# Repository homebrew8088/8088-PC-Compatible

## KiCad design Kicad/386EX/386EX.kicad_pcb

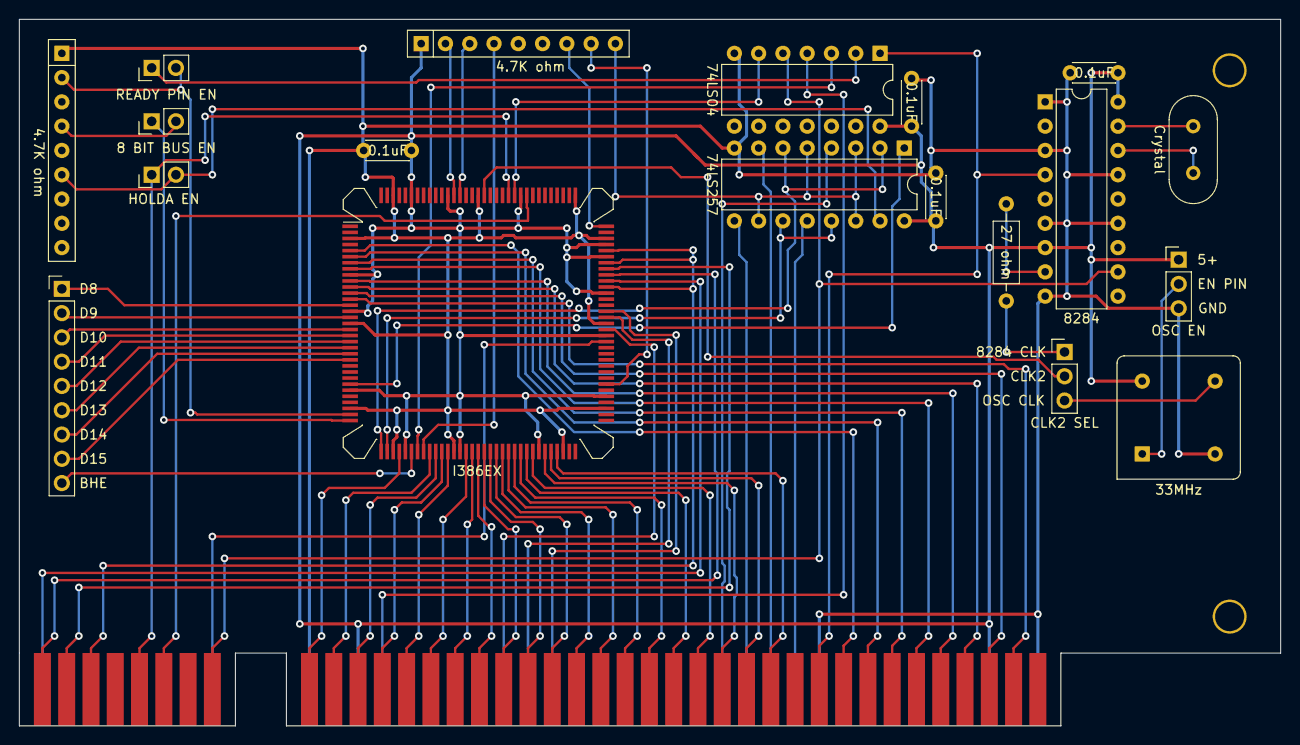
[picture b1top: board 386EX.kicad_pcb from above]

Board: 2 copper layers, 132.0 x 73.9 mm, 23 parts (0 on the bottom side), 79 nets.

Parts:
8_BIT_BUS_EN1: 8 BIT BUS EN; PinHeader_1x02_P2.54mm_Vertical
C1, C2, C3, C4: 0.1uF; C_Disc_D4.3mm_W1.9mm_P5.00mm
CLK2_SEL1: CLK2 SEL; PinHeader_1x03_P2.54mm_Vertical
HOLDA_EN1: HOLDA EN; PinHeader_1x02_P2.54mm_Vertical
J1: Conn_02x08_Counter_Clockwise; 16_EDGE_CARD_BUS
J2: Bus_ISA_8bit; BUS_8_BIT
J8: Conn_01x09; PinHeader_1x09_P2.54mm_Vertical
OSC_EN1: OSC EN; PinHeader_1x03_P2.54mm_Vertical
R: L; Large_Via
R1, R7: 4.7K ohm; R_Array_SIP9
R3: 27 ohm; R_Axial_DIN0207_L6.3mm_D2.5mm_P10.16mm_Horizontal
R#2: L; Large_Via
READY_PIN_EN1: READY PIN EN; PinHeader_1x02_P2.54mm_Vertical
U1: I386EX; PQFP-132_24x24mm_P0.635mm_i386
U2: 8284; DIP-18_W7.62mm
U3: 74LS257; DIP-16_W7.62mm
U4: 74LS04; DIP-14_W7.62mm
X1: 33MHz; Oscillator_DIP-8
Y1: Crystal; Crystal_HC18-U_Vertical

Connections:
/5+: C1.2, C2.2, C3.2, C4.2, J2.3, J2.29, OSC_EN1.1, R7.1, U1.9, U1.15, U1.28, U1.38, U1.47, U1.60, U1.71, U1.81, U1.88, U1.94, U1.96, U1.109, U1.121, U1.127, U2.7, U2.18, U3.16, U4.14, X1.8
/8_BIT_EN: 8_BIT_BUS_EN1.2, R1.4
/8_BIT_EN_JMP: 8_BIT_BUS_EN1.1, U1.33
/8284_OUT: CLK2_SEL1.1, R3.2
/A0: J2.62, U1.37
/A1: J2.61, U1.42
/A2: J2.60, U1.43
/A3: J2.59, U1.44
/A4: J2.58, U1.45
/A5: J2.57, U1.48
/A6: J2.56, U1.49
/A7: J2.55, U1.50
/A8: J2.54, U1.51
/A9: J2.53, U1.52
/A10: J2.52, U1.53
/A11: J2.51, U1.54
/A12: J2.50, U1.55
/A13: J2.49, U1.56
/A14: J2.48, U1.57
/A15: J2.47, U1.58
/A16: J2.46, U1.59
/A17: J2.45, U1.61
/A18: J2.44, U1.62
/A19: J2.43, U1.63
/ALE: J2.28, U4.4
/ALE_: U1.40, U4.3
/BHE: J8.9, U1.39
/CLK1: R3.1, U2.8
/CLK2: CLK2_SEL1.2, U1.115
/D0: J2.40, U1.5
/D1: J2.39, U1.6
/D2: J2.38, U1.7
/D3: J2.37, U1.8
/D4: J2.36, U1.10
/D5: J2.35, U1.11
/D6: J2.34, U1.12
/D7: J2.33, U1.13
/D8: J8.1, U1.14
/D9: J8.2, U1.16
/D10: J8.3, U1.18
/D11: J8.4, U1.19
/D12: J8.5, U1.20
/D13: J8.6, U1.21
/D14: J8.7, U1.22
/D15: J8.8, U1.23
/FLT: R7.7, U1.99
/GND: C1.1, C2.1, C3.1, C4.1, J2.1, J2.10, J2.31, OSC_EN1.3, R1.1, U1.3, U1.17, U1.31, U1.36, U1.46, U1.64, U1.69, U1.83, U1.97, U1.100, U1.116, U1.130, U2.1, U2.3, U2.6, U2.9, U2.13, U2.15, U3.8, U4.7, X1.4
/HF_PCLK: J1.11, U1.89, U1.93, U1.95
/HOLD: J1.14, U1.108
/HOLDA: HOLDA_EN1.1, J1.13, U1.111
/HOLDA_JMP: HOLDA_EN1.2, R1.6, U3.15
/IORD: J2.14, U3.4
/IOWR: J2.13, U3.9
/IO_M: U1.27, U3.1
/IRQ1: J1.1, U1.80
/IRQ5: J2.23, U1.82
/IRQ6: J2.22, U1.84
/IRQ7: J2.21, U1.85
/MRD: J2.12, U3.7
/MWR: J2.11, U3.12
/NMI: J1.8, U1.90
/OSC_EN: OSC_EN1.2, X1.1
/OSC_OUTPUT: CLK2_SEL1.3, X1.5
/PIPELINE_EN: R7.4, U1.41
/PU_257: R7.9, U3.3, U3.5, U3.10, U3.14
/RD: U1.34, U3.2, U3.6
/RDY1: J2.41, U2.4, U4.1
/READY_: READY_PIN_EN1.1, U4.2
/READY_JMP: R1.2, READY_PIN_EN1.2, U1.32
/RESET: J1.16, U2.11, U4.5
/RESET_: U1.110, U4.6
/SMI: R7.8, U1.73
/SMIACT: R7.2, U1.120
/SPK_GO: J1.10, U1.92
/SPK_OUT: J1.9, U1.91
/TRST: R7.3, U1.119
/WR: U1.35, U3.11, U3.13
/X1: U2.17, Y1.1
/X2: U2.16, Y1.2

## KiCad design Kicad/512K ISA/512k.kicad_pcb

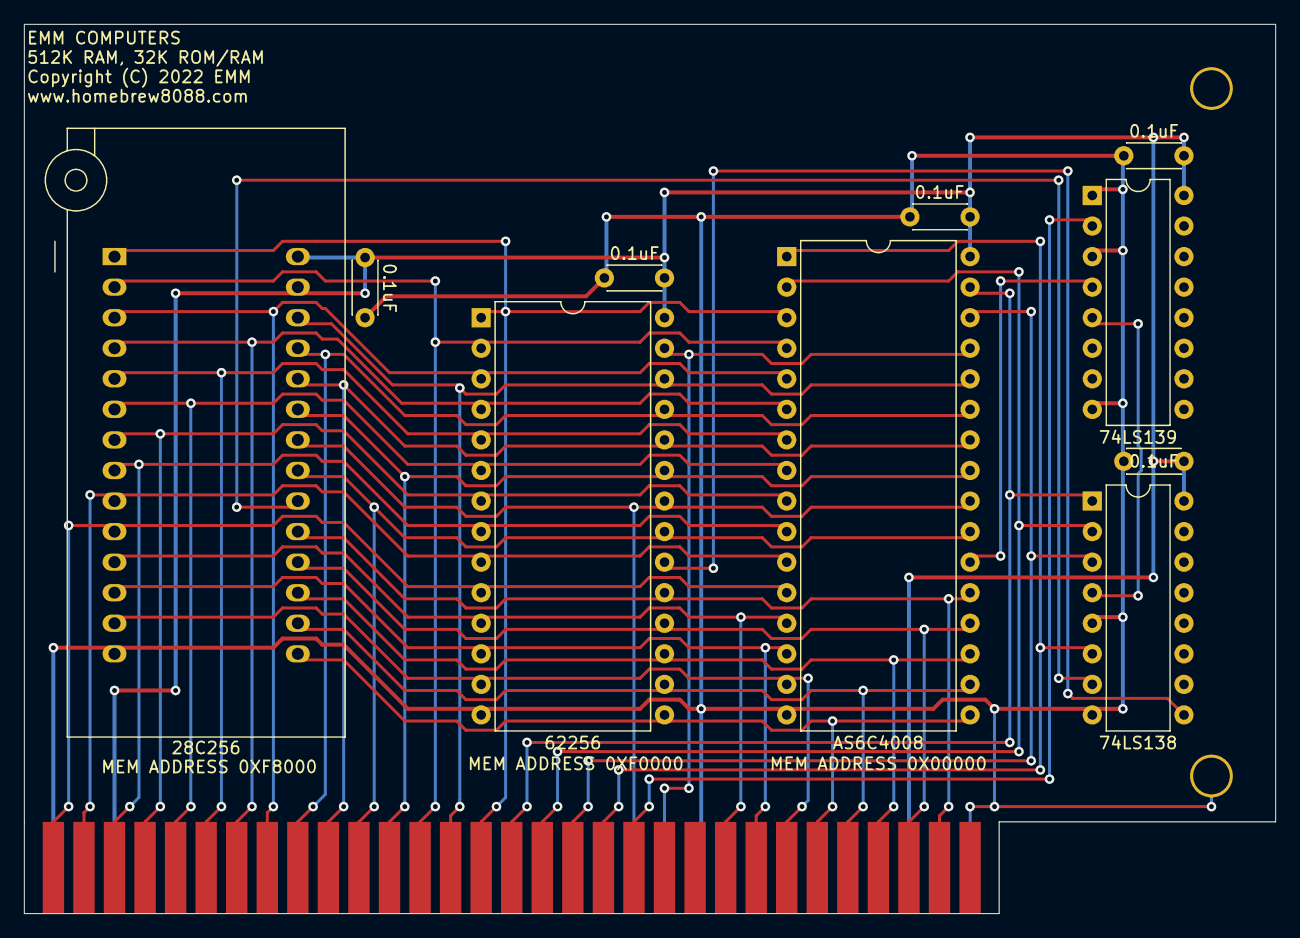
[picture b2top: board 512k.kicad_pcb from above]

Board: 2 copper layers, 104.0 x 73.9 mm, 13 parts (0 on the bottom side), 36 nets.

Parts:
C1, C2, C3, C4, C5: 0.1uF; C_Disc_D4.3mm_W1.9mm_P5.00mm
J9: Bus_ISA_8bit; BUS_8_BIT
R: L; Large_Via
R#2: L; Large_Via
U1: 62256; DIP-28_W15.24mm
U2: 28C256; DIP_Socket-28_W11.9_W12.7_W15.24_W17.78_W18.5_3M_228-1277-0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
U3: AS6C4008; DIP-32_W15.24mm
U4: 74LS139; DIP-16_W7.62mm
U5: 74LS138; DIP-16_W7.62mm

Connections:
/5+: C1.2, C2.2, C3.2, C4.2, C5.2, J9.3, J9.29, U1.28, U2.27, U2.28, U3.32, U4.16, U5.16
/32K_RAM_CS: U1.20, U5.9
/32K_ROM_CS: U2.20, U5.7
/512K_CS: U3.22, U4.4
/A0: J9.62, U1.10, U2.10, U3.12
/A1: J9.61, U1.9, U2.9, U3.11
/A2: J9.60, U1.8, U2.8, U3.10
/A3: J9.59, U1.7, U2.7, U3.9
/A4: J9.58, U1.6, U2.6, U3.8
/A5: J9.57, U1.5, U2.5, U3.7
/A6: J9.56, U1.4, U2.4, U3.6
/A7: J9.55, U1.3, U2.3, U3.5
/A8: J9.54, U1.25, U2.25, U3.27
/A9: J9.53, U1.24, U2.24, U3.26
/A10: J9.52, U1.21, U2.21, U3.23
/A11: J9.51, U1.23, U2.23, U3.25
/A12: J9.50, U1.2, U2.2, U3.4
/A13: J9.49, U1.26, U2.26, U3.28
/A14: J9.48, U1.1, U2.1, U3.3
/A15: J9.47, U3.31, U5.1
/A16: J9.46, U3.2, U5.2
/A17: J9.45, U3.30, U5.3
/A18: J9.44, U3.1, U5.6
/A19: J9.43, U4.2
/D0: J9.40, U1.11, U2.11, U3.13
/D1: J9.39, U1.12, U2.12, U3.14
/D2: J9.38, U1.13, U2.13, U3.15
/D3: J9.37, U1.15, U2.15, U3.17
/D4: J9.36, U1.16, U2.16, U3.18
/D5: J9.35, U1.17, U2.17, U3.19
/D6: J9.34, U1.18, U2.18, U3.20
/D7: J9.33, U1.19, U2.19, U3.21
/GND: C1.1, C2.1, C3.1, C4.1, C5.1, J9.1, J9.10, J9.31, R.1, U1.14, U2.14, U3.16, U4.1, U4.3, U4.8, U5.5, U5.8
/MRD: J9.12, U1.22, U2.22, U3.24
/MWR: J9.11, U1.27, U3.29
/UPPER_512K: U4.5, U5.4

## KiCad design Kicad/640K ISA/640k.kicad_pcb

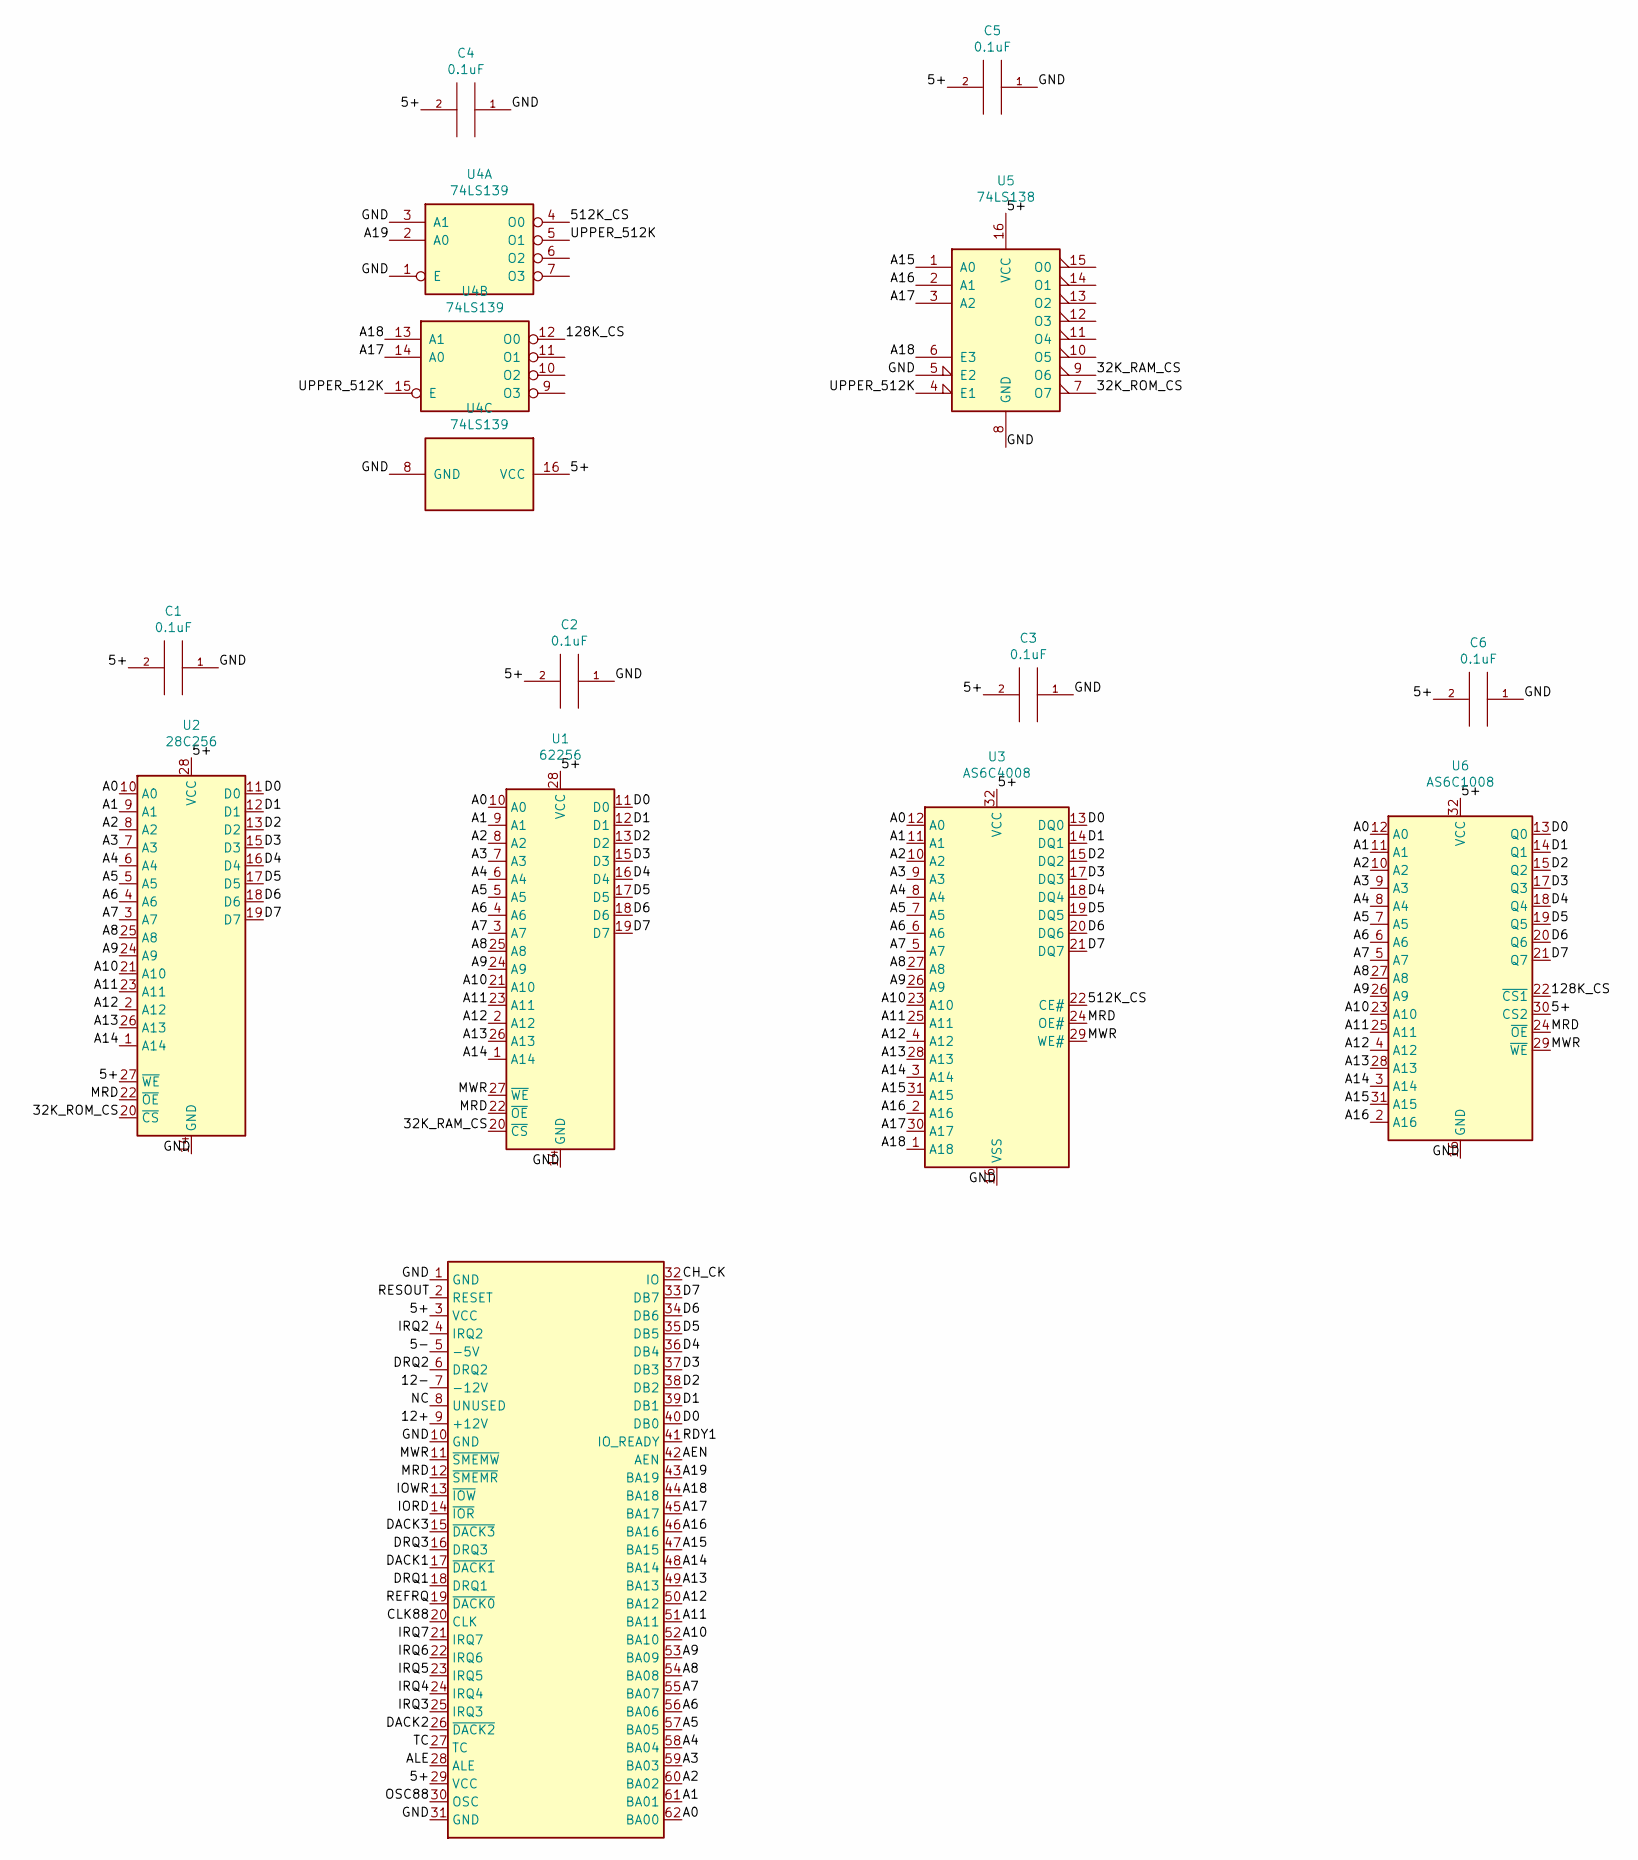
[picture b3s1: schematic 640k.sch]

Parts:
C1, C2, C3, C4, C5, C6: 0.1uF; C_Disc_D4.3mm_W1.9mm_P5.00mm
J9: Bus_ISA_8bit; BUS_8_BIT
U1: 62256; DIP-28_W15.24mm
U2: 28C256; DIP-28_W15.24mm
U3: AS6C4008; DIP-32_W15.24mm
U4: 74LS139; DIP-16_W7.62mm
U5: 74LS138; DIP-16_W7.62mm
U6: AS6C1008; DIP-32_W15.24mm

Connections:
/5+: C1.2, C2.2, C3.2, C4.2, C5.2, C6.2, J9.3 (VCC), J9.29 (VCC), U1.28 (VCC), U2.27 (~WE), U2.28 (VCC), U3.32 (VCC), U4.16 (VCC), U5.16 (VCC), U6.30 (CS2), U6.32 (VCC)
/5-: J9.5 (-5V)
/12+: J9.9 (+12V)
/12-: J9.7 (-12V)
/32K_RAM_CS: U1.20 (~CS), U5.9 (O6)
/32K_ROM_CS: U2.20 (~CS), U5.7 (O7)
/128K_CS: U4.12 (O0), U6.22 (~CS1)
/512K_CS: U3.22 (CE#), U4.4 (O0)
/A0: J9.62 (BA00), U1.10 (A0), U2.10 (A0), U3.12 (A0), U6.12 (A0)
/A1: J9.61 (BA01), U1.9 (A1), U2.9 (A1), U3.11 (A1), U6.11 (A1)
/A2: J9.60 (BA02), U1.8 (A2), U2.8 (A2), U3.10 (A2), U6.10 (A2)
/A3: J9.59 (BA03), U1.7 (A3), U2.7 (A3), U3.9 (A3), U6.9 (A3)
/A4: J9.58 (BA04), U1.6 (A4), U2.6 (A4), U3.8 (A4), U6.8 (A4)
/A5: J9.57 (BA05), U1.5 (A5), U2.5 (A5), U3.7 (A5), U6.7 (A5)
/A6: J9.56 (BA06), U1.4 (A6), U2.4 (A6), U3.6 (A6), U6.6 (A6)
/A7: J9.55 (BA07), U1.3 (A7), U2.3 (A7), U3.5 (A7), U6.5 (A7)
/A8: J9.54 (BA08), U1.25 (A8), U2.25 (A8), U3.27 (A8), U6.27 (A8)
/A9: J9.53 (BA09), U1.24 (A9), U2.24 (A9), U3.26 (A9), U6.26 (A9)
/A10: J9.52 (BA10), U1.21 (A10), U2.21 (A10), U3.23 (A10), U6.23 (A10)
/A11: J9.51 (BA11), U1.23 (A11), U2.23 (A11), U3.25 (A11), U6.25 (A11)
/A12: J9.50 (BA12), U1.2 (A12), U2.2 (A12), U3.4 (A12), U6.4 (A12)
/A13: J9.49 (BA13), U1.26 (A13), U2.26 (A13), U3.28 (A13), U6.28 (A13)
/A14: J9.48 (BA14), U1.1 (A14), U2.1 (A14), U3.3 (A14), U6.3 (A14)
/A15: J9.47 (BA15), U3.31 (A15), U5.1 (A0), U6.31 (A15)
/A16: J9.46 (BA16), U3.2 (A16), U5.2 (A1), U6.2 (A16)
/A17: J9.45 (BA17), U3.30 (A17), U4.14 (A0), U5.3 (A2)
/A18: J9.44 (BA18), U3.1 (A18), U4.13 (A1), U5.6 (E3)
/A19: J9.43 (BA19), U4.2 (A0)
/AEN: J9.42 (AEN)
/ALE: J9.28 (ALE)
/CH_CK: J9.32 (IO)
/CLK88: J9.20 (CLK)
/D0: J9.40 (DB0), U1.11 (D0), U2.11 (D0), U3.13 (DQ0), U6.13 (Q0)
/D1: J9.39 (DB1), U1.12 (D1), U2.12 (D1), U3.14 (DQ1), U6.14 (Q1)
/D2: J9.38 (DB2), U1.13 (D2), U2.13 (D2), U3.15 (DQ2), U6.15 (Q2)
/D3: J9.37 (DB3), U1.15 (D3), U2.15 (D3), U3.17 (DQ3), U6.17 (Q3)
/D4: J9.36 (DB4), U1.16 (D4), U2.16 (D4), U3.18 (DQ4), U6.18 (Q4)
/D5: J9.35 (DB5), U1.17 (D5), U2.17 (D5), U3.19 (DQ5), U6.19 (Q5)
/D6: J9.34 (DB6), U1.18 (D6), U2.18 (D6), U3.20 (DQ6), U6.20 (Q6)
/D7: J9.33 (DB7), U1.19 (D7), U2.19 (D7), U3.21 (DQ7), U6.21 (Q7)
/DACK1: J9.17 (~DACK1)
/DACK2: J9.26 (~DACK2)
/DACK3: J9.15 (~DACK3)
/DRQ1: J9.18 (DRQ1)
/DRQ2: J9.6 (DRQ2)
/DRQ3: J9.16 (DRQ3)
/GND: C1.1, C2.1, C3.1, C4.1, C5.1, C6.1, J9.1 (GND), J9.10 (GND), J9.31 (GND), U1.14 (GND), U2.14 (GND), U3.16 (VSS), U4.1 (E), U4.3 (A1), U4.8 (GND), U5.5 (E2), U5.8 (GND), U6.16 (GND); also elsewhere on the board
/IORD: J9.14 (~IOR)
/IOWR: J9.13 (~IOW)
/IRQ2: J9.4 (IRQ2)
/IRQ3: J9.25 (IRQ3)
/IRQ4: J9.24 (IRQ4)
/IRQ5: J9.23 (IRQ5)
/IRQ6: J9.22 (IRQ6)
/IRQ7: J9.21 (IRQ7)
/MRD: J9.12 (~SMEMR), U1.22 (~OE), U2.22 (~OE), U3.24 (OE#), U6.24 (~OE)
/MWR: J9.11 (~SMEMW), U1.27 (~WE), U3.29 (WE#), U6.29 (~WE)
/NC: J9.8 (UNUSED)
/OSC88: J9.30 (OSC)
/RDY1: J9.41 (IO_READY)
/REFRQ: J9.19 (~DACK0)
/RESOUT: J9.2 (RESET)
/TC: J9.27 (TC)
/UPPER_512K: U4.5 (O1), U4.15 (E), U5.4 (E1)

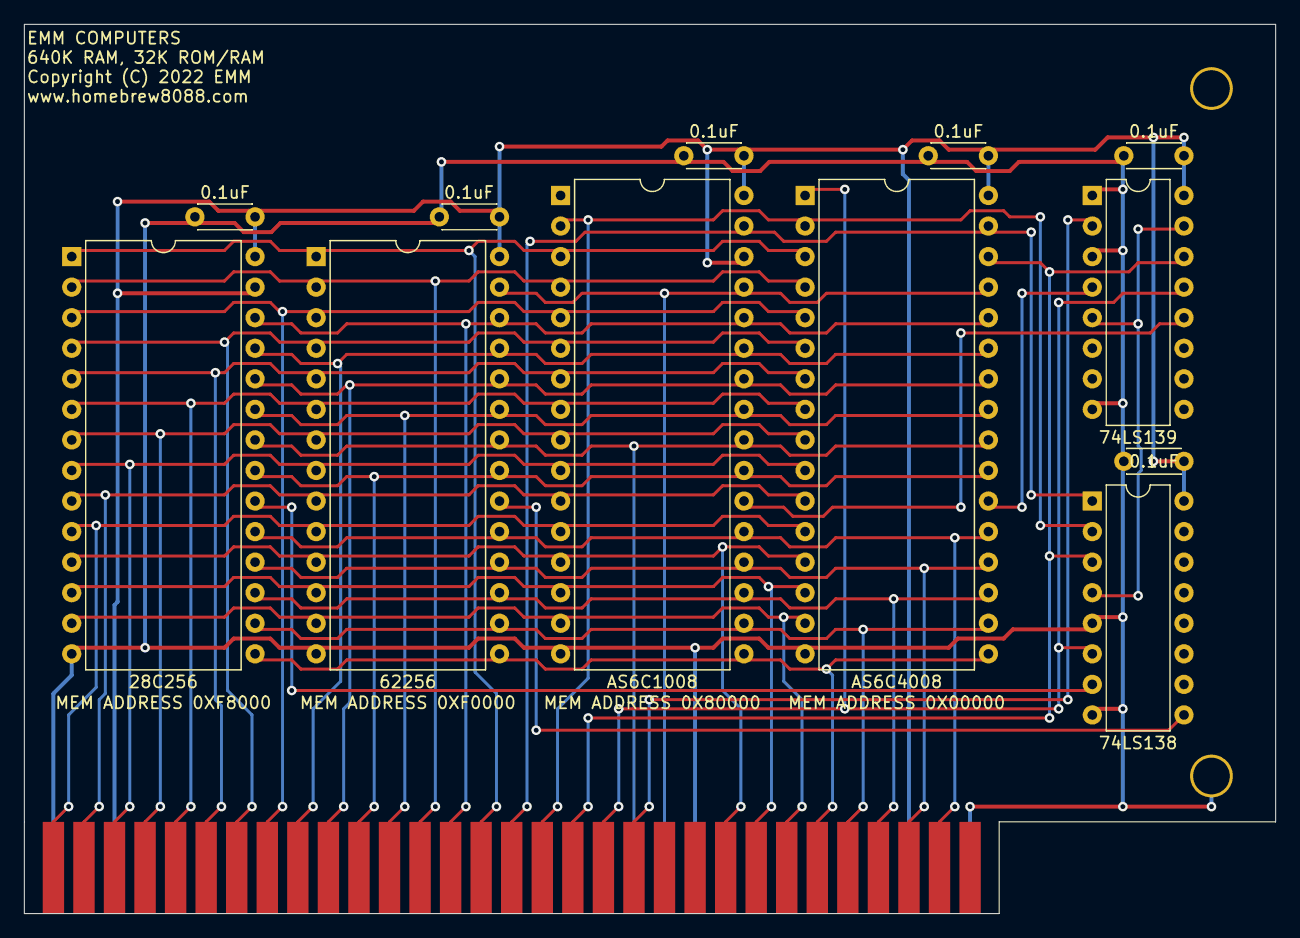
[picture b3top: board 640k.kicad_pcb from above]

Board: 2 copper layers, 104.0 x 73.9 mm, 15 parts (0 on the bottom side), 37 nets.

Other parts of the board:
R: L; Large_Via
R#2: L; Large_Via

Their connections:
/GND: R.1; also elsewhere on the board

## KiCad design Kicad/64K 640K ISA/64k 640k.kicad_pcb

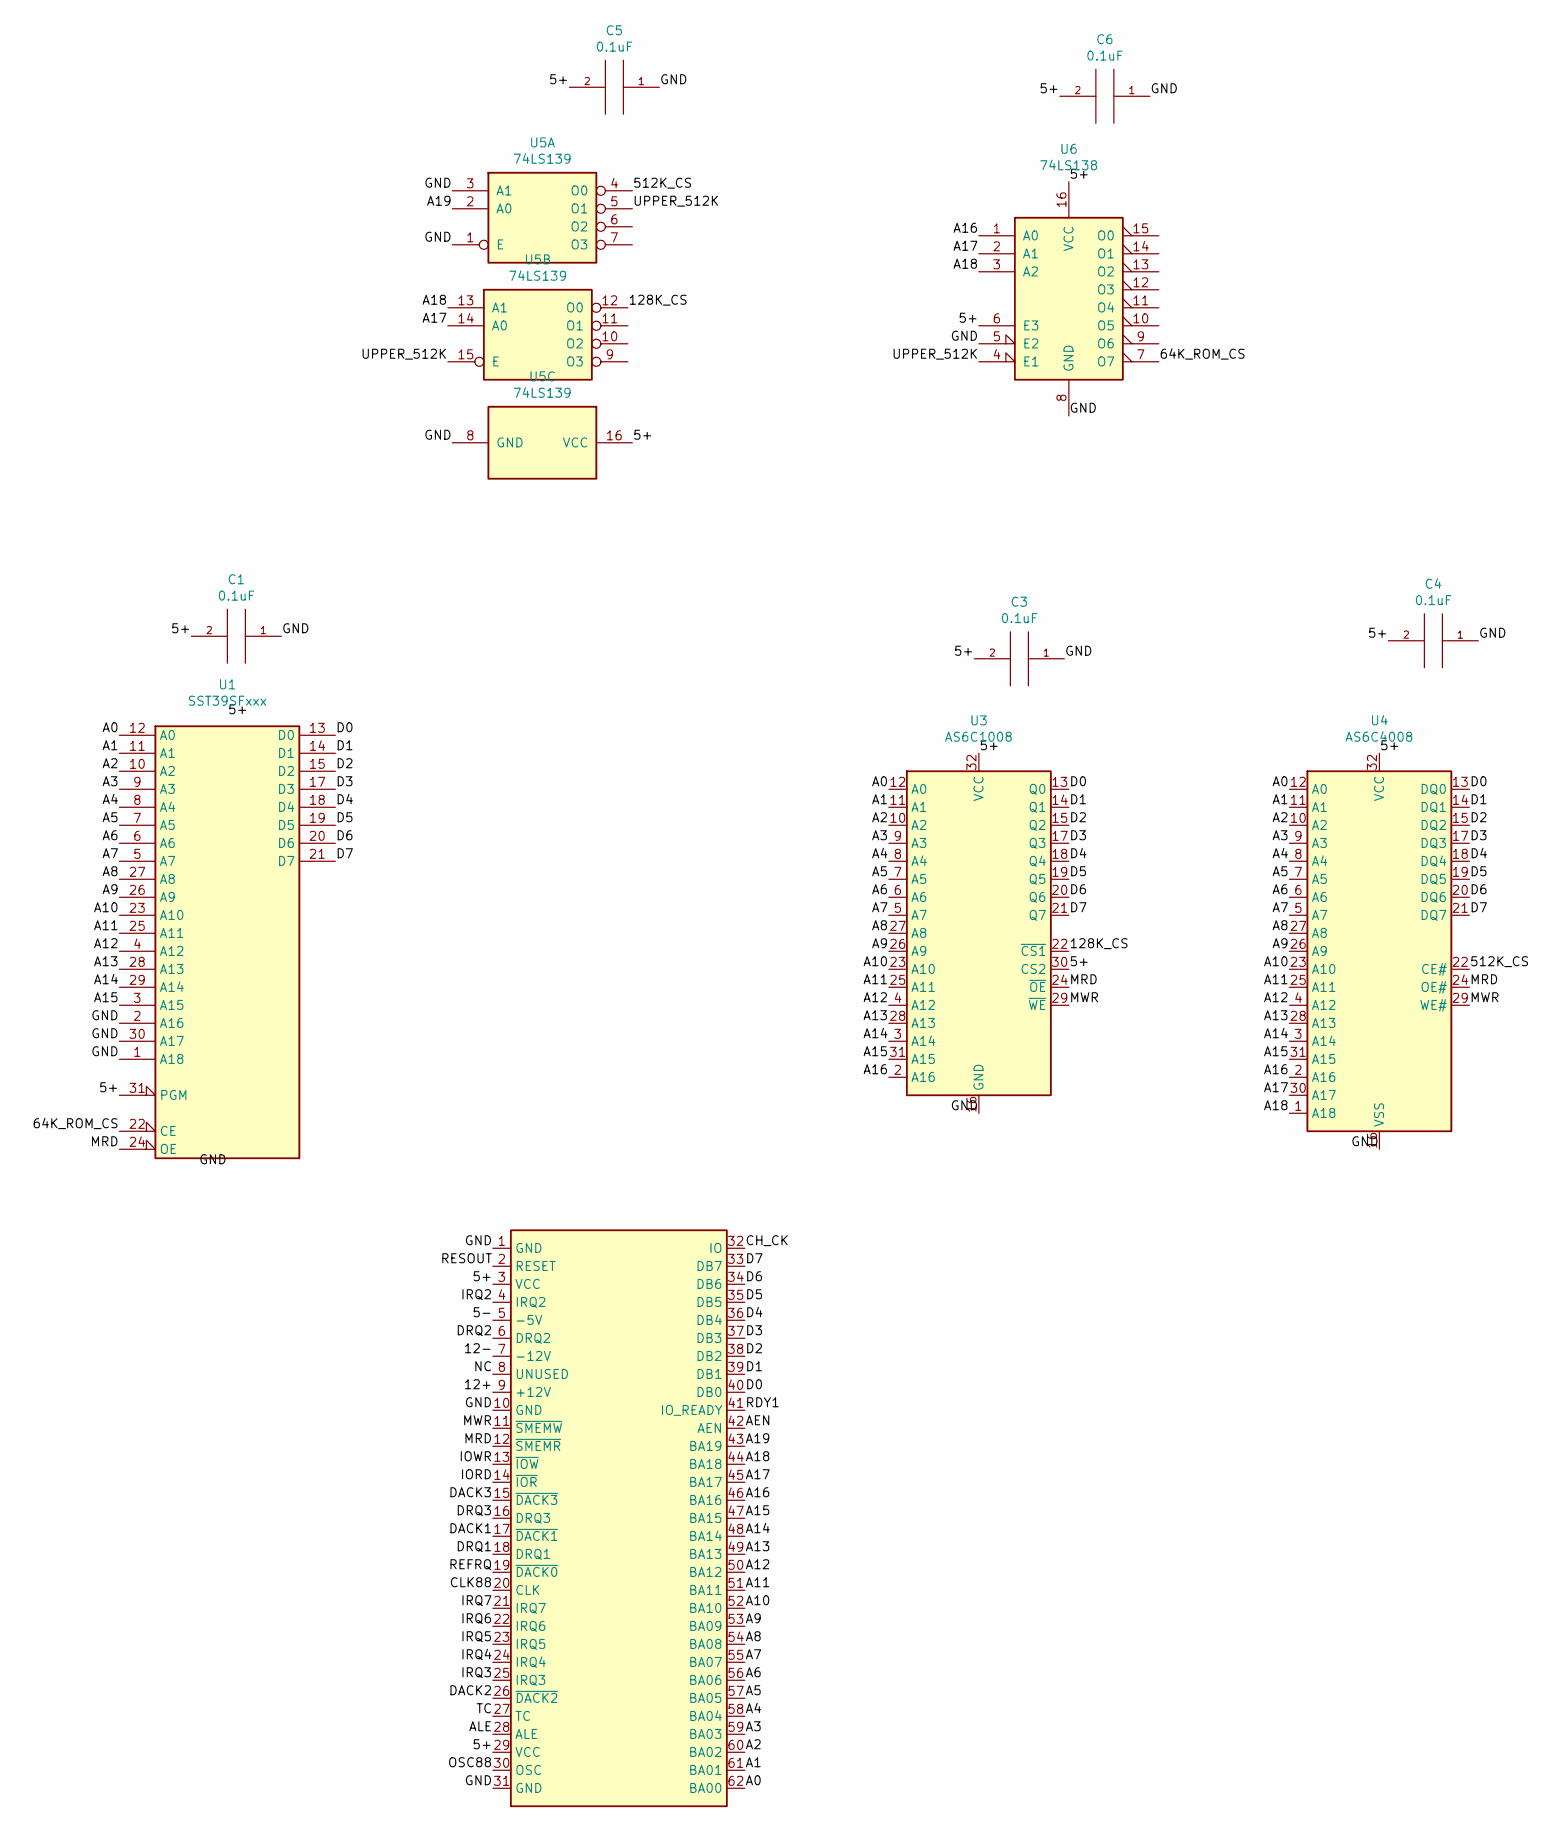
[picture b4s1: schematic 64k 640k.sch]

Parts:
C1, C3, C4, C5, C6: 0.1uF; C_Disc_D4.3mm_W1.9mm_P5.00mm
J9: Bus_ISA_8bit; BUS_8_BIT
U1: SST39SFxxx; DIP-32_W15.24mm
U3: AS6C1008; DIP-32_W15.24mm
U4: AS6C4008; DIP-32_W15.24mm
U5: 74LS139; DIP-16_W7.62mm
U6: 74LS138; DIP-16_W7.62mm

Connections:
/5-: J9.5 (-5V)
/12+: J9.9 (+12V)
/12-: J9.7 (-12V)
/64K_ROM_CS: U1.22 (CE), U6.7 (O7)
/128K_CS: U3.22 (~CS1), U5.12 (O0)
/512K_CS: U4.22 (CE#), U5.4 (O0)
/A0: J9.62 (BA00), U1.12 (A0), U3.12 (A0), U4.12 (A0)
/A1: J9.61 (BA01), U1.11 (A1), U3.11 (A1), U4.11 (A1)
/A2: J9.60 (BA02), U1.10 (A2), U3.10 (A2), U4.10 (A2)
/A3: J9.59 (BA03), U1.9 (A3), U3.9 (A3), U4.9 (A3)
/A4: J9.58 (BA04), U1.8 (A4), U3.8 (A4), U4.8 (A4)
/A5: J9.57 (BA05), U1.7 (A5), U3.7 (A5), U4.7 (A5)
/A6: J9.56 (BA06), U1.6 (A6), U3.6 (A6), U4.6 (A6)
/A7: J9.55 (BA07), U1.5 (A7), U3.5 (A7), U4.5 (A7)
/A8: J9.54 (BA08), U1.27 (A8), U3.27 (A8), U4.27 (A8)
/A9: J9.53 (BA09), U1.26 (A9), U3.26 (A9), U4.26 (A9)
/A10: J9.52 (BA10), U1.23 (A10), U3.23 (A10), U4.23 (A10)
/A11: J9.51 (BA11), U1.25 (A11), U3.25 (A11), U4.25 (A11)
/A12: J9.50 (BA12), U1.4 (A12), U3.4 (A12), U4.4 (A12)
/A13: J9.49 (BA13), U1.28 (A13), U3.28 (A13), U4.28 (A13)
/A14: J9.48 (BA14), U1.29 (A14), U3.3 (A14), U4.3 (A14)
/A15: J9.47 (BA15), U1.3 (A15), U3.31 (A15), U4.31 (A15)
/A16: J9.46 (BA16), U3.2 (A16), U4.2 (A16), U6.1 (A0)
/A17: J9.45 (BA17), U4.30 (A17), U5.14 (A0), U6.2 (A1)
/A18: J9.44 (BA18), U4.1 (A18), U5.13 (A1), U6.3 (A2)
/A19: J9.43 (BA19), U5.2 (A0)
/AEN: J9.42 (AEN)
/ALE: J9.28 (ALE)
/CH_CK: J9.32 (IO)
/CLK88: J9.20 (CLK)
/D0: J9.40 (DB0), U1.13 (D0), U3.13 (Q0), U4.13 (DQ0)
/D1: J9.39 (DB1), U1.14 (D1), U3.14 (Q1), U4.14 (DQ1)
/D2: J9.38 (DB2), U1.15 (D2), U3.15 (Q2), U4.15 (DQ2)
/D3: J9.37 (DB3), U1.17 (D3), U3.17 (Q3), U4.17 (DQ3)
/D4: J9.36 (DB4), U1.18 (D4), U3.18 (Q4), U4.18 (DQ4)
/D5: J9.35 (DB5), U1.19 (D5), U3.19 (Q5), U4.19 (DQ5)
/D6: J9.34 (DB6), U1.20 (D6), U3.20 (Q6), U4.20 (DQ6)
/D7: J9.33 (DB7), U1.21 (D7), U3.21 (Q7), U4.21 (DQ7)
/DACK1: J9.17 (~DACK1)
/DACK2: J9.26 (~DACK2)
/DACK3: J9.15 (~DACK3)
/DRQ1: J9.18 (DRQ1)
/DRQ2: J9.6 (DRQ2)
/DRQ3: J9.16 (DRQ3)
/IORD: J9.14 (~IOR)
/IOWR: J9.13 (~IOW)
/IRQ2: J9.4 (IRQ2)
/IRQ3: J9.25 (IRQ3)
/IRQ4: J9.24 (IRQ4)
/IRQ5: J9.23 (IRQ5)
/IRQ6: J9.22 (IRQ6)
/IRQ7: J9.21 (IRQ7)
/MRD: J9.12 (~SMEMR), U1.24 (OE), U3.24 (~OE), U4.24 (OE#)
/MWR: J9.11 (~SMEMW), U3.29 (~WE), U4.29 (WE#)
/NC: J9.8 (UNUSED)
/OSC88: J9.30 (OSC)
/RDY1: J9.41 (IO_READY)
/REFRQ: J9.19 (~DACK0)
/RESOUT: J9.2 (RESET)
/TC: J9.27 (TC)
/UPPER_512K: U5.5 (O1), U5.15 (E), U6.4 (E1)
GND: C1.1, C3.1, C4.1, C5.1, C6.1, J9.1 (GND), J9.10 (GND), J9.31 (GND), U1.1 (A18), U1.2 (A16), U1.16 (GND), U1.30 (A17), U3.16 (GND), U4.16 (VSS), U5.1 (E), U5.3 (A1), U5.8 (GND), U6.5 (E2), U6.8 (GND)
VCC: C1.2, C3.2, C4.2, C5.2, C6.2, J9.3 (VCC), J9.29 (VCC), U1.31 (PGM), U1.32 (VCC), U3.30 (CS2), U3.32 (VCC), U4.32 (VCC), U5.16 (VCC), U6.6 (E3), U6.16 (VCC)

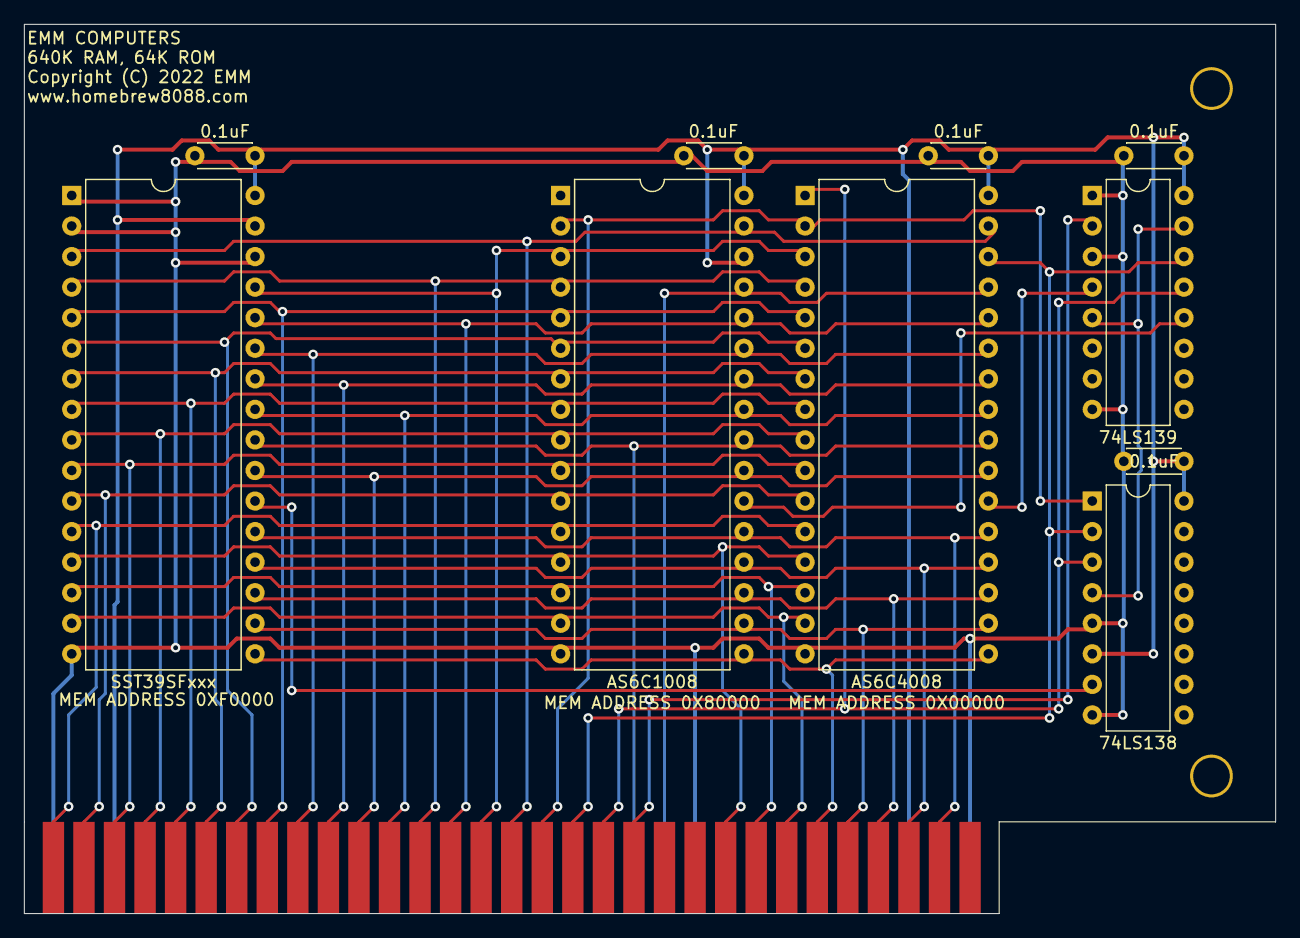
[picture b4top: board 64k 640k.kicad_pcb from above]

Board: 2 copper layers, 104.0 x 73.9 mm, 13 parts (0 on the bottom side), 36 nets.

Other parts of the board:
R: L; Large_Via
R#2: L; Large_Via

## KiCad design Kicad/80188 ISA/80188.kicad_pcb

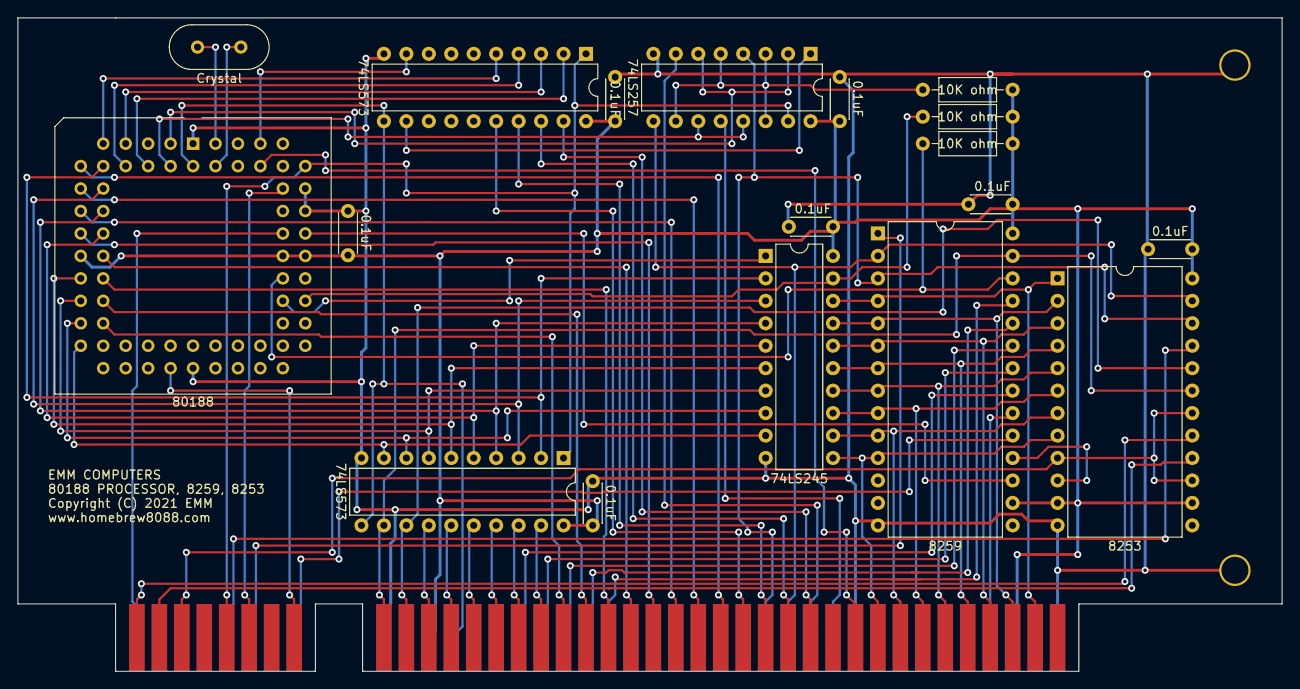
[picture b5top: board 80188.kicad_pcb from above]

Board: 2 copper layers, 143.0 x 73.9 mm, 22 parts (0 on the bottom side), 76 nets.

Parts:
80188: PLCC-68_THT-Socket
C2, C3, C4, C5, C6, C7, C8: 0.1uF; C_Disc_D4.3mm_W1.9mm_P5.00mm
J1: Conn_02x08_Counter_Clockwise; 16_EDGE_CARD_BUS
J9: Bus_ISA_8bit; BUS_8_BIT
R: L; Large_Via
R1, R2, R5: 10K ohm; R_Axial_DIN0207_L6.3mm_D2.5mm_P10.16mm_Horizontal
R#2: L; Large_Via
U2, U3: 74LS573; DIP-20_W7.62mm
U4: 74LS245; DIP-20_W7.62mm
U6: 8259; DIP-28_W15.24mm
U7: 8253; DIP-24_W15.24mm
U8: 74LS257; DIP-16_W7.62mm
Y1: Crystal; Crystal_HC18-U_Vertical

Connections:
/5+: 80188.9, 80188.43, 80188.44, C2.2, C3.2, C4.2, C5.2, C6.2, C7.2, C8.2, J9.3, J9.29, R1.2, R2.2, R5.2, U2.20, U3.20, U4.20, U6.16, U6.28, U7.11, U7.14, U7.24, U8.16
/A0: J9.62, U2.12, U6.27, U7.19
/A1: J9.61, U2.13, U7.20
/A2: J9.60, U2.14
/A3: J9.59, U2.15
/A4: J9.58, U2.16
/A5: J9.57, U2.17
/A6: J9.56, U2.18
/A7: J9.55, U2.19
/A8: 80188.16, J9.54
/A9: 80188.14, J9.53
/A10: 80188.12, J9.52
/A11: 80188.10, J9.51
/A12: 80188.7, J9.50
/A13: 80188.5, J9.49
/A14: 80188.3, J9.48
/A15: 80188.1, J9.47
/A16: J9.46, U3.16
/A16_: 80188.68, U3.5
/A17: J9.45, U3.17
/A17_: 80188.67, U3.4
/A18: J9.44, U3.18
/A18_: 80188.66, U3.3
/A19: J9.43, U3.19
/A19_: 80188.65, U3.2
/AD0: 80188.17, U2.9, U4.9
/AD1: 80188.15, U2.8, U4.8
/AD2: 80188.13, U2.7, U4.7
/AD3: 80188.11, U2.6, U4.6
/AD4: 80188.8, U2.5, U4.5
/AD5: 80188.6, U2.4, U4.4
/AD6: 80188.4, U2.3, U4.3
/AD7: 80188.2, U2.2, U4.2
/ALE: 80188.61, J9.28, U2.11, U3.11
/D0: J9.40, U4.11, U6.11, U7.8
/D1: J9.39, U4.12, U6.10, U7.7
/D2: J9.38, U4.13, U6.9, U7.6
/D3: J9.37, U4.14, U6.8, U7.5
/D4: J9.36, U4.15, U6.7, U7.4
/D5: J9.35, U4.16, U6.6, U7.3
/D6: J9.34, U4.17, U6.5, U7.2
/D7: J9.33, U4.18, U6.4, U7.1
/DEN: 80188.39, R1.1, U4.19
/DTR: 80188.40, U4.1
/GND: 80188.26, 80188.47, 80188.49, 80188.60, C2.1, C3.1, C4.1, C5.1, C6.1, C7.1, C8.1, J9.1, J9.10, J9.31, R.1, R#2.1, U2.10, U3.10, U4.10, U6.14, U7.12, U8.8
/HF_PCLK: J1.11, U7.9, U7.15, U7.18
/HOLD: 80188.50, J1.14
/HOLDA: 80188.51, J1.13, U2.1, U3.1, U8.15
/INTA: 80188.42, R2.1, U6.26
/INTR: 80188.45, U6.17
/IORD: J9.14, U6.3, U7.22, U8.4
/IOWR: J9.13, U6.2, U7.23, U8.9
/IO_002X: J1.3, U6.1
/IO_004X: J1.4, U7.21
/IO_M: U3.12, U8.1
/IRQ0: U6.18, U7.10
/IRQ1: J1.1, U6.19
/IRQ2: J9.4, U6.20
/IRQ3: J9.25, U6.21
/IRQ4: J9.24, U6.22
/IRQ5: J9.23, U6.23
/IRQ6: J9.22, U6.24
/IRQ7: J9.21, U6.25
/MRD: J9.12, U8.7
/MWR: J9.11, U8.12
/NMI: 80188.46, J1.8
/PU1: R5.1, U8.3, U8.5, U8.10, U8.14
/RD: 80188.62, U8.2, U8.6
/RDY1: 80188.55, J9.41
/RESET: 80188.24, J1.16
/S2: 80188.54, U3.9
/SPK_GO: J1.10, U7.16
/SPK_OUT: J1.9, U7.17
/WR: 80188.63, U8.11, U8.13
/X1: 80188.59, Y1.2
/X2: 80188.58, Y1.1

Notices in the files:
Kicad/512K ISA/512k.kicad_pcb:
Copyright (C) 2022 EMM
Kicad/80188 ISA/80188.kicad_pcb:
Copyright (C) 2021 EMM
